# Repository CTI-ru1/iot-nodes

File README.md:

# iot-nodes

The overall design for the installation of IoT infrastructure has been built upon the open-source (hardware and software) Arduino
platform and consist of:
-  Environmental Devices (Digital and Analog versions)
-  Power Meter Devices
-  Gateway

The Eagles files and BOM of materials for the first for all the IoT nodes can be found it in the respective folders and the Arduino programs too. 
The Gateway program can be found it on (link)

Libraries
--
- App.h Has been designed to include the overall application on your Arduino IoT node program. Manage the add of the different sensor connected to the node, collect the data from each one and the update cloud values through the under tree network. You can find the code on this repository. 
- For each each sensor include it on the IoT node a specific class is include it. The specific classes using on this platform can be found on UberdustSensor folder. If you want to include new ones just create a new sensor class, include it in the UbersdustSensor.h file and programming the follow methods as you need. 
	-	periodic_check(): will be called on each Arduino loop. Include here, for example a code if you want to read a sensor value faster that each 20 sec and calculated the averaage value.
	-	check_and_send(void): will be called once each 20 seconds. Then all the collected values will be updated in the cloud. Here you must give to the status parameter the final value to be update on.
			
- At the network level: Treerouting.h library is using on the creation of a tree network between all the IoT nodes, with the Gateway as root. Can be downloaded from (link)
- At physical and data link later we use IEEE802.15.4 communication with XBee devices connected to each IoT node using the Arduino XBee(Link) library and XBeeRadio library(link). We must notice here that on both libraries need to be modified the serial port for using with the Arduino Por Micro.On this case you just need to change the code in order to read from Serial1.

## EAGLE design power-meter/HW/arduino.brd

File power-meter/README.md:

# power-meter
IoT nodes 3-phases Power Meter with electricity to monitor the consumption of a building. The power consumption meter measures the apparent power in a three
phase electrical installation and calculates its true power consumption re-motely.
Communication with the device is achieved using IEEE 802.15.4 trough a gateway.
Find the eagle files and BOM of materials necessary for reproducing the device on the HW folder and the specific Arduino program on SW folder.

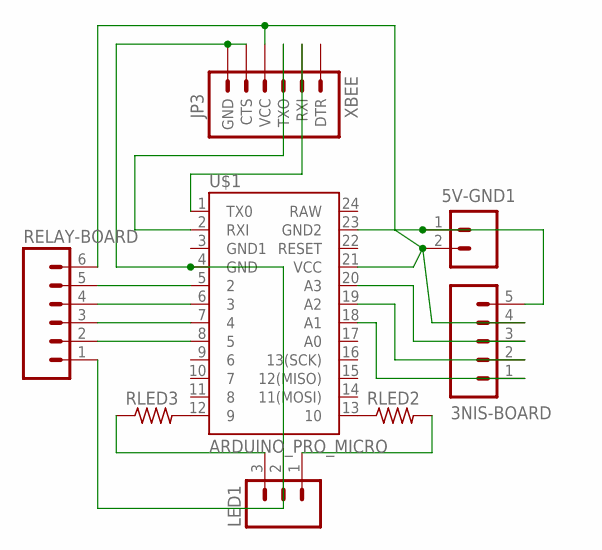
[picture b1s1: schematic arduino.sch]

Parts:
3NIS-BOARD: M05PTH; 1X05
5V-GND1: M025MM; SCREWTERMINAL-5MM-2
JP3: XBEE; 1X06
LED1: M03PTH; 1X03
RELAY-BOARD: M06SIP; 1X06
RLED2, RLED3: R-US_M0805; M0805
U$1: ARDUINO_PRO_MICRO

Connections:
unnamed: JP3.5 (CTS), JP3.6 (GND), LED1.2, RELAY-BOARD.1, U$1.4 (GND)
unnamed: 3NIS-BOARD.4, 5V-GND1.2, JP3.4 (VCC), RELAY-BOARD.6, U$1.21 (VCC)
unnamed: 3NIS-BOARD.3, U$1.20 (A3)
unnamed: RELAY-BOARD.5, U$1.5 (2)
unnamed: RELAY-BOARD.4, U$1.6 (3)
unnamed: RELAY-BOARD.3, U$1.7 (4)
unnamed: RELAY-BOARD.2, U$1.8 (5)
unnamed: JP3.2 (RXI), U$1.1 (TX0)
unnamed: 3NIS-BOARD.2, U$1.19 (A2)
unnamed: JP3.3 (TXO), U$1.2 (RXI)
unnamed: 3NIS-BOARD.1, U$1.18 (A1)
unnamed: RLED2.1, U$1.13 (10)
unnamed: RLED3.2, U$1.12 (9)
unnamed: LED1.1, RLED2.2
unnamed: LED1.3, RLED3.1
unnamed: 3NIS-BOARD.5, 5V-GND1.1, U$1.23 (GND2)

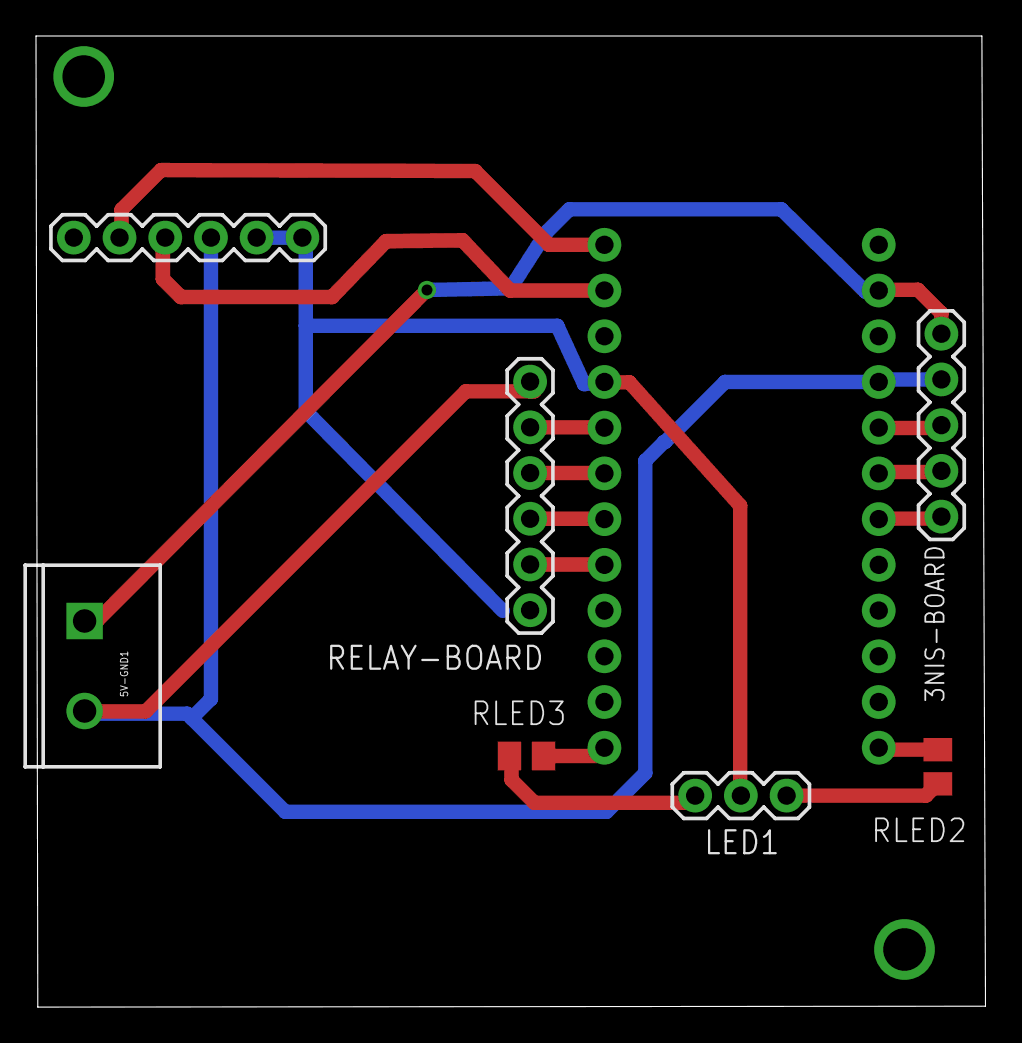
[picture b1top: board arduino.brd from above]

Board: 2 copper layers, 52.8 x 53.9 mm, 8 parts (0 on the bottom side), 16 nets.

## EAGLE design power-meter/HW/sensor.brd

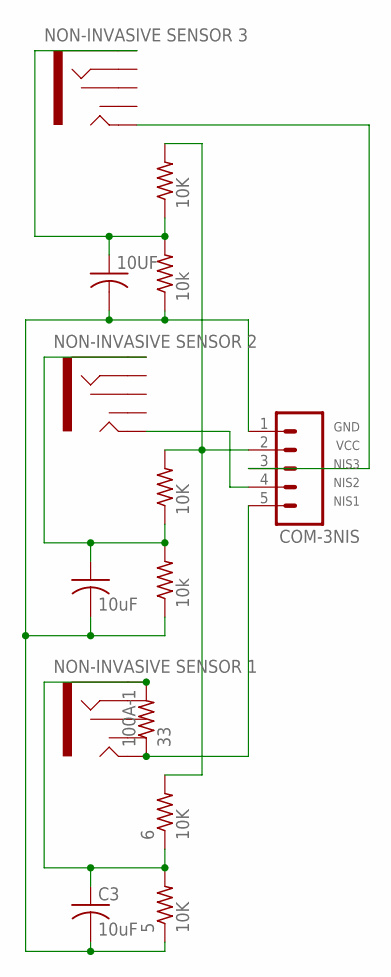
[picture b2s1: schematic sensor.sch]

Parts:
1, 3: 10k; M0805
2, 4, 5, 6: 10K; M0805
10UF: C-USC0805K; C0805K
100A-1: 33; M0805
C2, C3: 10uF; C0805K
COM-3NIS: M05PTH; 1X05
U1: NON-INVASIVE SENSOR 1; AUDIO-JACK
U2: NON-INVASIVE SENSOR 2; AUDIO-JACK
U3: NON-INVASIVE SENSOR 3; AUDIO-JACK

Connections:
unnamed: 2.2, 4.2, 6.2, COM-3NIS.2
unnamed 1: COM-3NIS.3, U3.TIP; also elsewhere on the board
unnamed 2: COM-3NIS.4, U2.TIP; also elsewhere on the board
unnamed: 100A-1.1, COM-3NIS.5, U1.TIP
unnamed 4: 1.2, 2.1, 10UF.1, U3.SLEEVE; also elsewhere on the board
unnamed 5: 3.2, 4.1, C2.1, U2.SLEEVE; also elsewhere on the board
unnamed: 5.2, 6.1, 100A-1.2, C3.1, U1.SLEEVE
unnamed: 1.1, 3.1, 5.1, 10UF.2, C2.2, C3.2, COM-3NIS.1

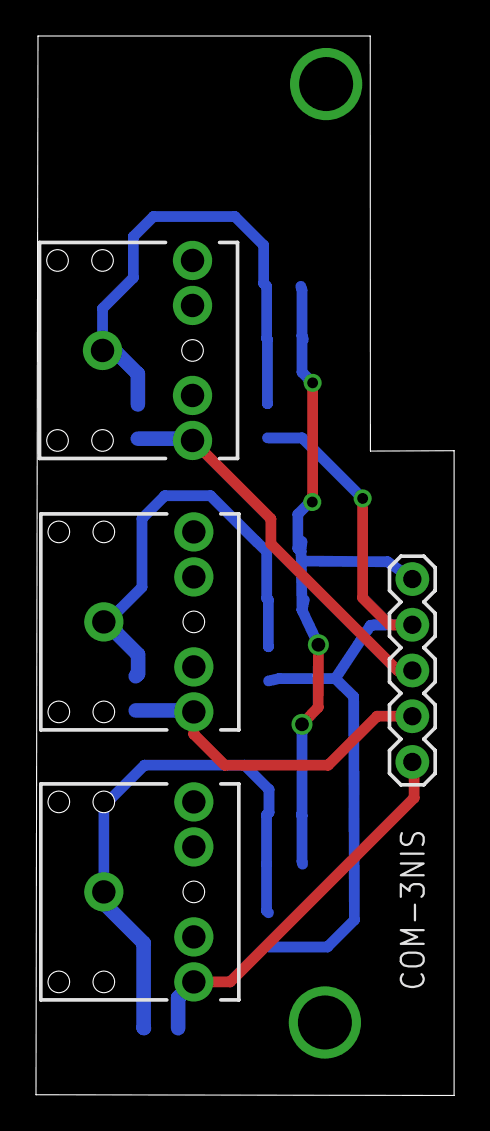
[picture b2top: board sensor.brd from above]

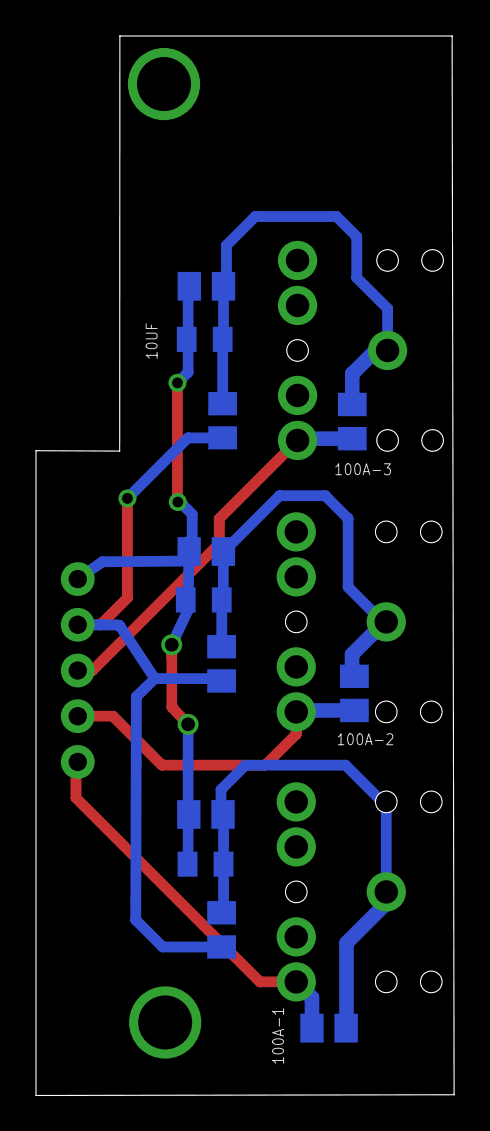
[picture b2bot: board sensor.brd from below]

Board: 2 copper layers, 23.2 x 58.9 mm, 16 parts (12 on the bottom side), 8 nets.

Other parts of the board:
100A-2, 100A-3: 33; M0805

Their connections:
unnamed 1: 100A-3.1; also elsewhere on the board
unnamed 2: 100A-2.1; also elsewhere on the board
unnamed 4: 100A-3.2; also elsewhere on the board
unnamed 5: 100A-2.2; also elsewhere on the board

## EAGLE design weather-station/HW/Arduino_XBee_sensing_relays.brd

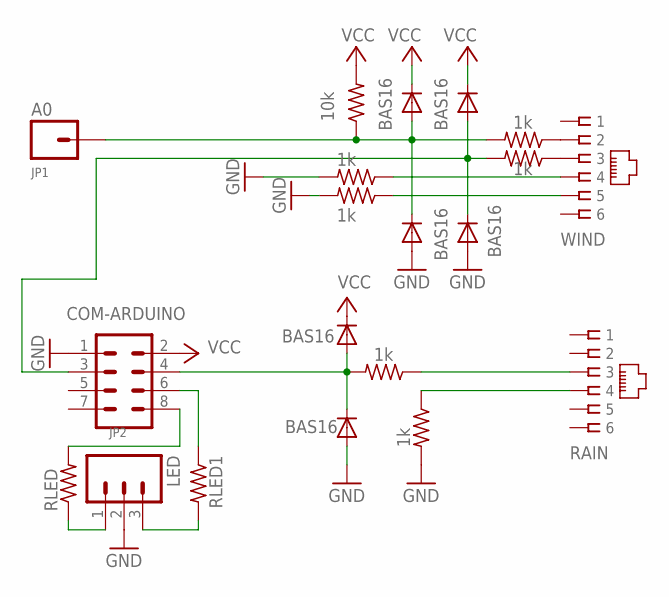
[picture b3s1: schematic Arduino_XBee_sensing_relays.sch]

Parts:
A0: JP1; 1X01
COM-ARDUINO: JP2; 2X4
D1, D2, D3, D4, D5, D6: BAS16; SOD-323
LED: M03PTH; 1X03
R1, R3, R4, R5, R7, R8: 1k; M0805
R2: 10k; M0805
RAIN: RAIN; RJ11-NO_SHIELD
RLED, RLED1: R-US_M0805; M0805
WIND: WIND; RJ11-NO_SHIELD

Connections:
GND: COM-ARDUINO.1, D2.2 (A), D4.2 (A), D6.2 (A), LED.2, R4.2, R5.2, R8.2
unnamed: COM-ARDUINO.4, D5.2 (A), D6.1 (C), R7.2
unnamed: LED.1, RLED.1
unnamed: R1.1, WIND.2
unnamed: R7.1, RAIN.3
unnamed: A0.1, D1.2 (A), D2.1 (C), R1.2, R2.1
unnamed: LED.3, RLED1.2
unnamed: COM-ARDUINO.6, RLED1.1
unnamed: COM-ARDUINO.8, RLED.2
unnamed: COM-ARDUINO.3, D3.2 (A), D4.1 (C), R3.2
unnamed: R4.1, WIND.4
unnamed: R5.1, WIND.5
unnamed: R8.1, RAIN.4
unnamed: R3.1, WIND.3
VCC: COM-ARDUINO.2, D1.1 (C), D3.1 (C), D5.1 (C), R2.2

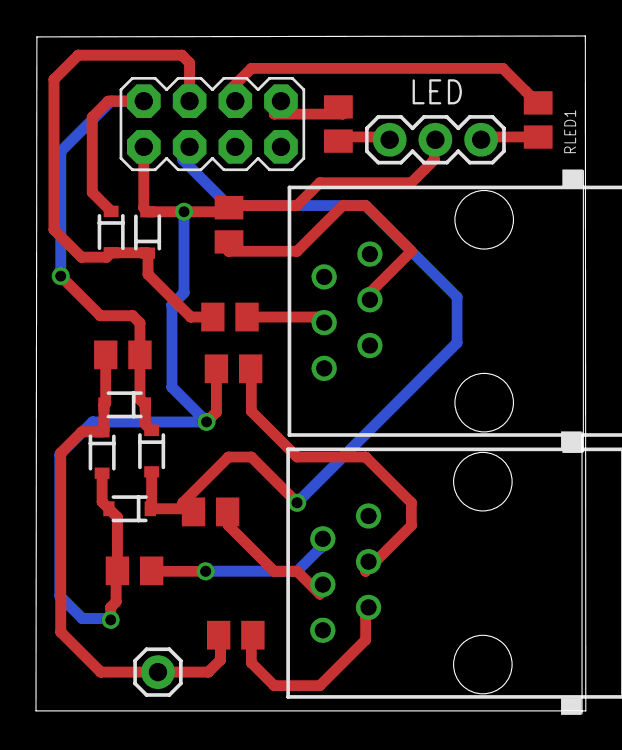
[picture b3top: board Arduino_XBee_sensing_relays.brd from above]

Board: 2 copper layers, 30.5 x 37.6 mm, 20 parts (0 on the bottom side), 15 nets.

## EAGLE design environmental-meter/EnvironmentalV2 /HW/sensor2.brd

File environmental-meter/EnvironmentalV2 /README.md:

# environmental-meter V1
IoT Environmental V2 include: 
- Grove-module with THO2 digital temperature and humidity sensor
- Grove-module with TSL2560 digital light sensor
- Grove-Sound sensor 
- PIR motion sensor.
Find the eagle files and BOM of materials necessary for reproducing the device on the HW folder and the specific Arduino program on SW folder. 
Is also necessary download the specific library for each digital module:
- Light module library: https://github.com/Seeed-Studio/Grove_Digital_Light_Sensor. 
- TH02 sensor has been modified and can be found it at https://github.com/CTI-ru1/Grove_Temper_Humidity_TH02. Here we have modified the original Seed-Studio library in order to 
can connect to the same I2C bus many digital sensors. We include methods to power on/off the module for guarantee just one module power each time on the I2C bus.

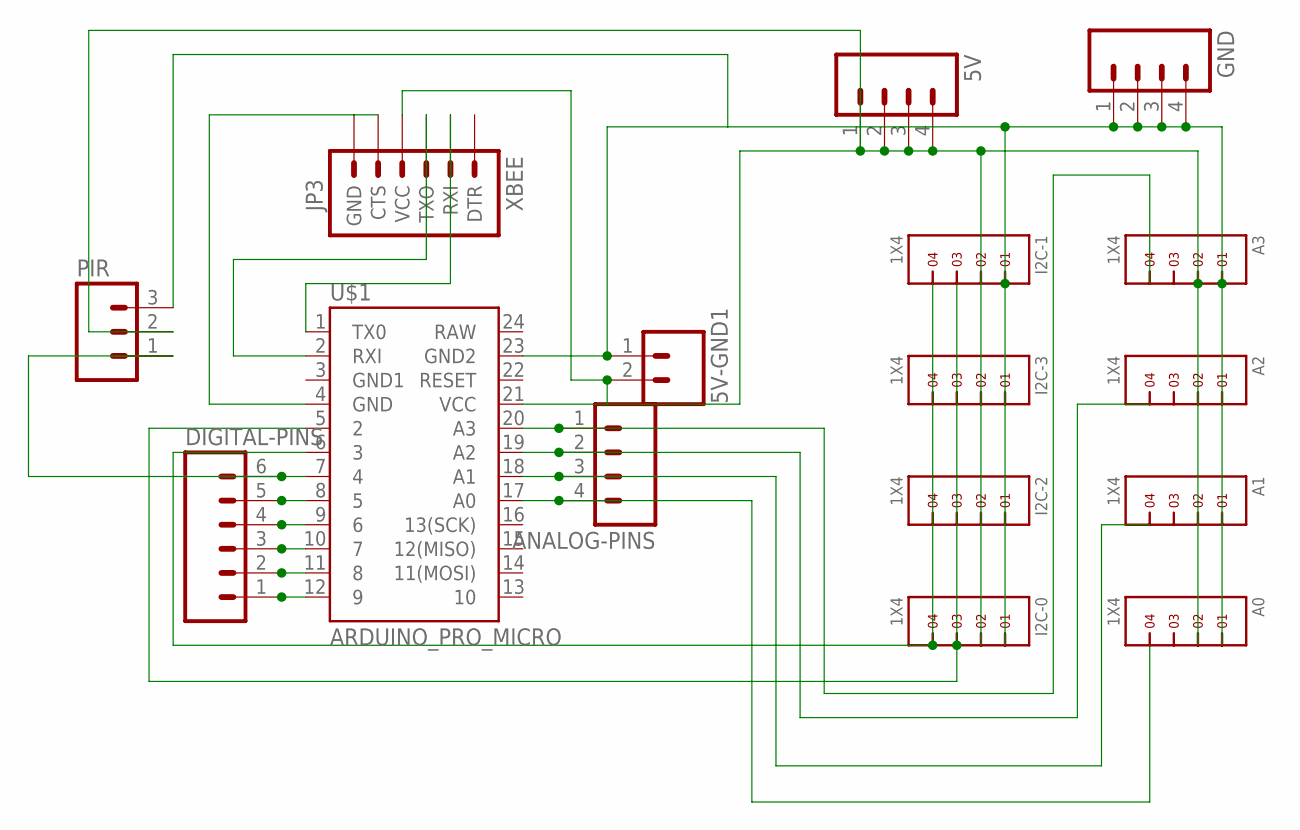
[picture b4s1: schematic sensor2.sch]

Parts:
5V: M04; 04P
5V-GND1: M025MM; SCREWTERMINAL-5MM-2
A0, A1, A2, A3: 1X4
ANALOG-PINS: M04; 04P
DIGITAL-PINS: M06; 06P
GND: M04; 04P
I2C-0, I2C-1, I2C-2, I2C-3: 1X4
JP3: XBEE; 1X06
PIR: M03; 03P
U$1: ARDUINO_PRO_MICRO

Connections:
GND: 5V-GND1.1, A0.1, A1.1, A2.1, A3.1, GND.1, GND.2, GND.3, GND.4, I2C-0.1, I2C-1.1, I2C-2.1, I2C-3.1, PIR.3, U$1.23 (GND2)
unnamed: I2C-0.4, I2C-1.4, I2C-2.4, I2C-3.4, U$1.6 (3)
unnamed: A3.4, ANALOG-PINS.1, U$1.20 (A3)
unnamed: JP3.5 (CTS), JP3.6 (GND), U$1.4 (GND)
unnamed: I2C-0.3, I2C-1.3, I2C-2.3, I2C-3.3, U$1.5 (2)
unnamed: 5V.1, 5V.2, 5V.3, 5V.4, 5V-GND1.2, A0.2, A1.2, A2.2, A3.2, I2C-0.2, I2C-1.2, I2C-2.2, I2C-3.2, JP3.4 (VCC), PIR.2, U$1.21 (VCC)
unnamed: A2.4, ANALOG-PINS.2, U$1.19 (A2)
unnamed: A1.4, ANALOG-PINS.3, U$1.18 (A1)
unnamed: JP3.2 (RXI), U$1.1 (TX0)
unnamed: A0.4, ANALOG-PINS.4, U$1.17 (A0)
unnamed: JP3.3 (TXO), U$1.2 (RXI)
unnamed: DIGITAL-PINS.2, U$1.11 (8)
unnamed: DIGITAL-PINS.3, U$1.10 (7)
unnamed: DIGITAL-PINS.4, U$1.9 (6)
unnamed: DIGITAL-PINS.5, U$1.8 (5)
unnamed: DIGITAL-PINS.6, PIR.1, U$1.7 (4)
unnamed: DIGITAL-PINS.1, U$1.12 (9)

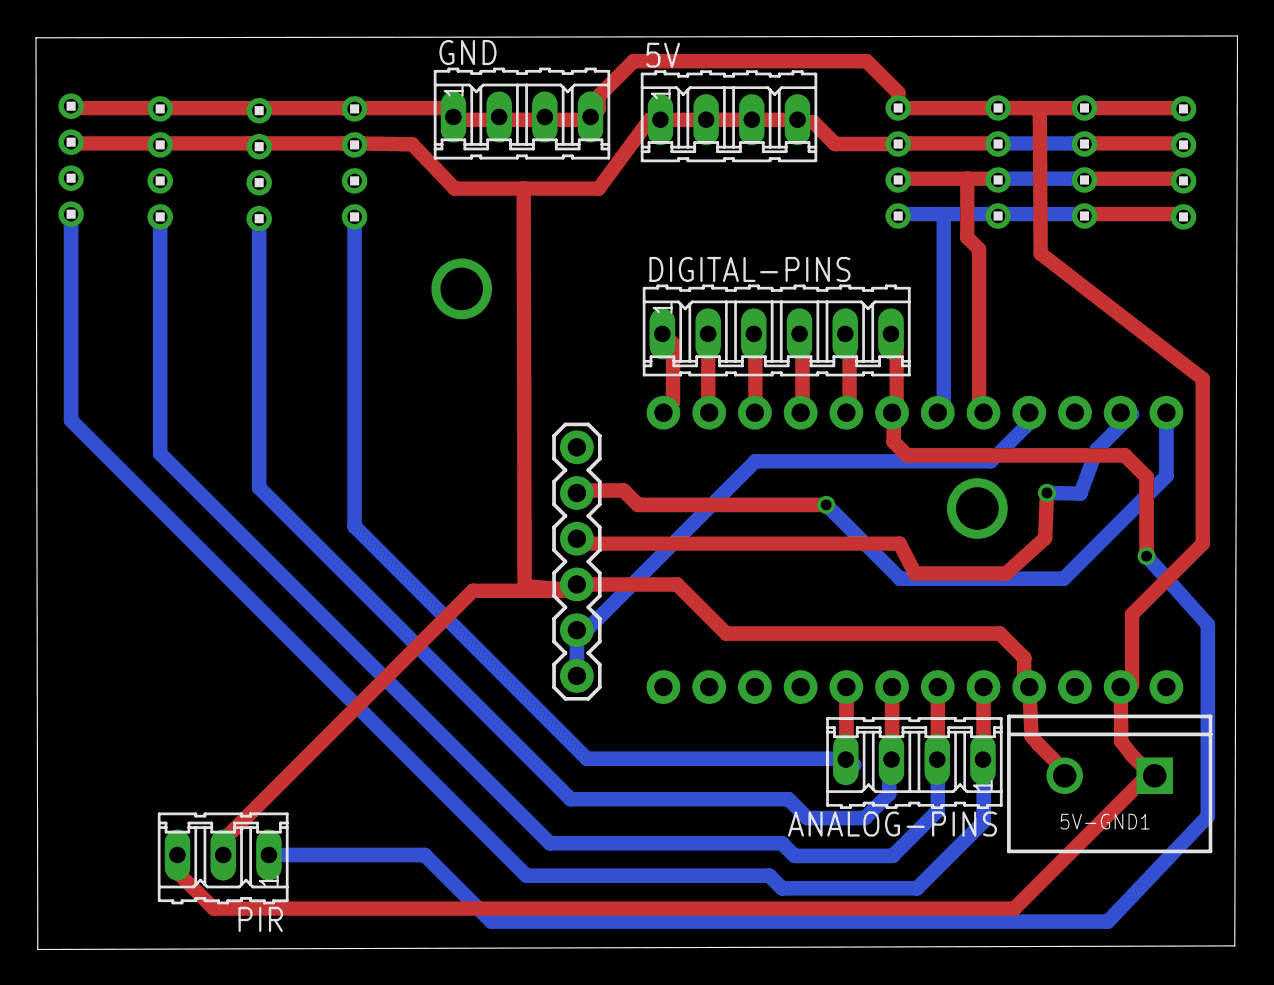
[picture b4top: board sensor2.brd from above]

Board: 2 copper layers, 66.8 x 50.7 mm, 16 parts (0 on the bottom side), 17 nets.

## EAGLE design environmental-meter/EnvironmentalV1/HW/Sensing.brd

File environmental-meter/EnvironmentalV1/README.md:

# environmental-meter V1
IoT Environmental V1 include: 

- LM35 analog temperature sensor
- HIH-4030 analog humidity sensor 
- photo-resistor
- Grove-Sound sensor 
- PIR motion sensor

Find the eagle files and BOM of materials necessary for reproducing the device on the HW folder and the specific Arduino program on SW folder.

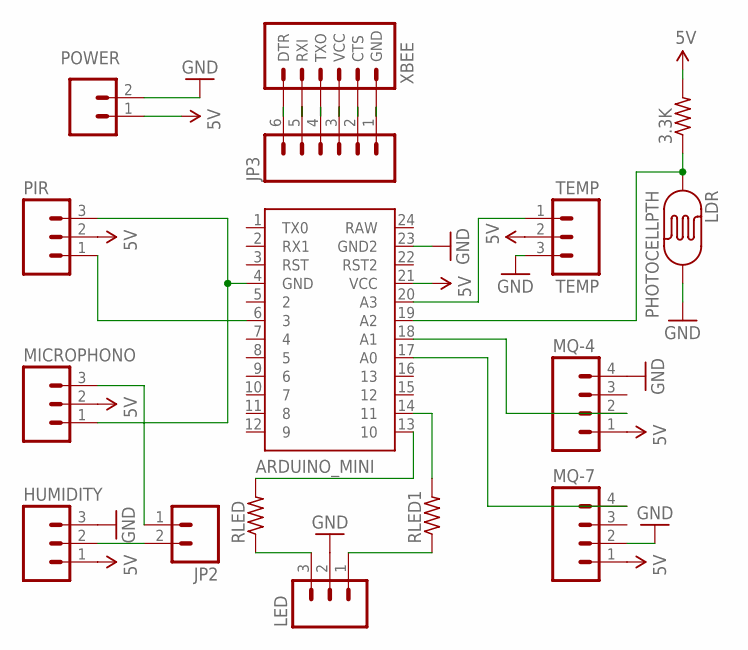
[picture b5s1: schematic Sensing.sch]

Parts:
3.3K: R-US_M0805; M0805
ARDUINO_MINI: ARDUINO_MINI
HUMIDITY: HUMIDITY; 1X03
JP2: M02PTH; 1X02
JP3: M06SIP; 1X06
LDR: PHOTOCELLPTH; PHOTOCELL
LED: M03PTH; 1X03
MICROPHONO: M03PTH; 1X03
MQ-4, MQ-7: M04PTH; 1X04
PIR: M03PTH; 1X03
POWER: M025MM; SCREWTERMINAL-5MM-2
RLED, RLED1: R-US_M0805; M0805
TEMP: TEMP; 1X03_NO_SILK
XBEE: ARDUINO_SERIAL_PROGRAMPTH; 1X06

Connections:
5V: 3.3K.2, ARDUINO_MINI.21 (VCC), HUMIDITY.1, MICROPHONO.2, MQ-4.1, MQ-7.1, PIR.2, POWER.1, TEMP.2
EXTRA_SENS_OUT: ARDUINO_MINI.20 (A3), TEMP.1
GND: ARDUINO_MINI.23 (GND2), HUMIDITY.3, LDR.2, LED.2, MQ-4.4, MQ-7.2, POWER.2, TEMP.3
HUMIDITY: HUMIDITY.2, JP2.2
MQ4_(CH4)_SENS_OUT: ARDUINO_MINI.18 (A1), MQ-4.2
MQ7_(CO)_SENS_OUT: ARDUINO_MINI.17 (A0), MQ-7.4
unnamed: LED.1, RLED1.1
unnamed: LED.3, RLED.1
unnamed: ARDUINO_MINI.6 (3), PIR.1
unnamed: ARDUINO_MINI.4 (GND), MICROPHONO.1, PIR.3
unnamed: JP3.6, XBEE.1 (DTR)
unnamed: JP3.5, XBEE.2 (RXI)
unnamed: JP3.4, XBEE.3 (TXO)
unnamed: JP3.3, XBEE.4 (VCC)
unnamed: JP3.2, XBEE.5 (CTS)
unnamed: JP3.1, XBEE.6 (GND)
unnamed: 3.3K.1, ARDUINO_MINI.19 (A2), LDR.1
unnamed: ARDUINO_MINI.14 (11), RLED1.2
unnamed: JP2.1, MICROPHONO.3
unnamed: ARDUINO_MINI.13 (10), RLED.2

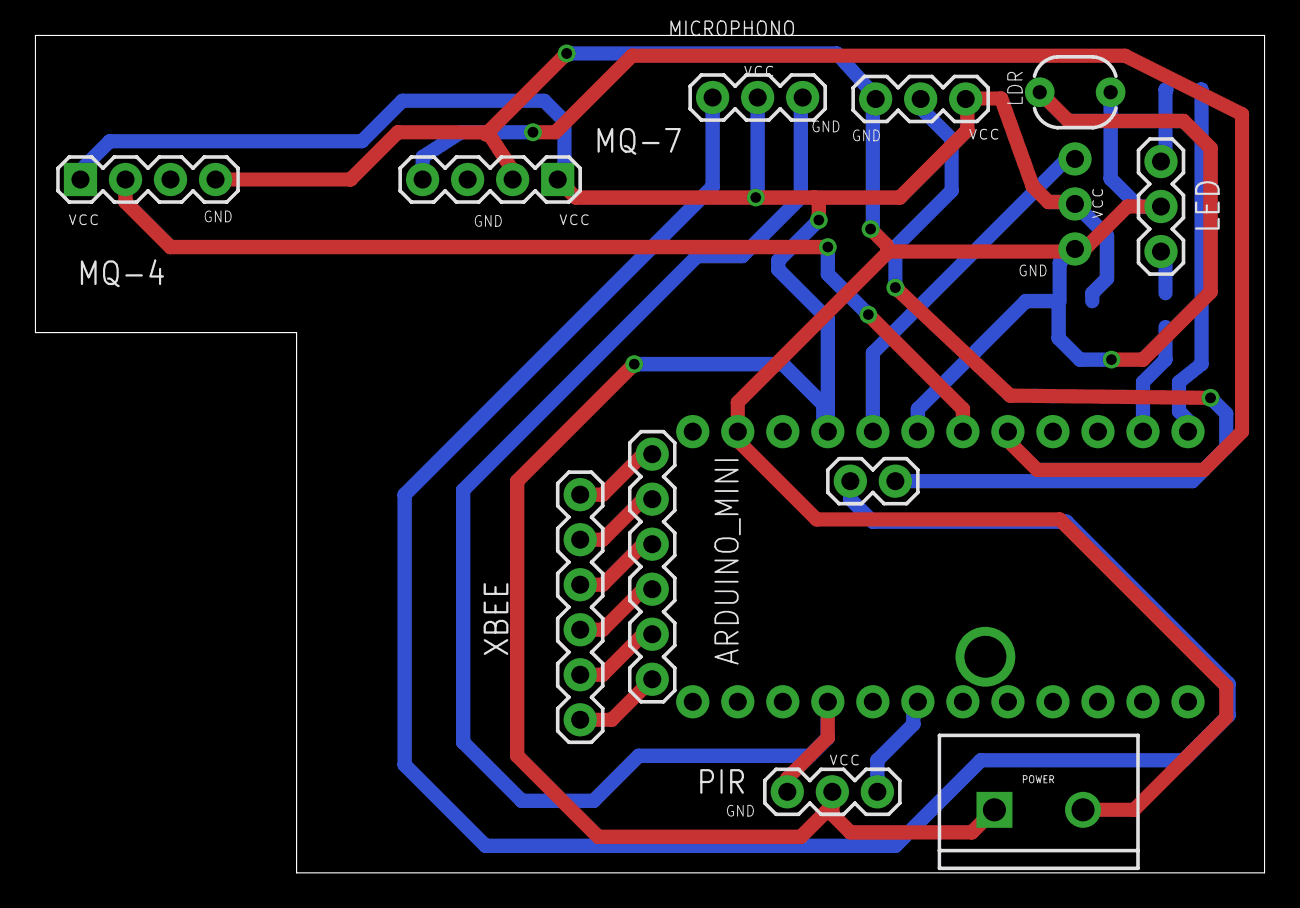
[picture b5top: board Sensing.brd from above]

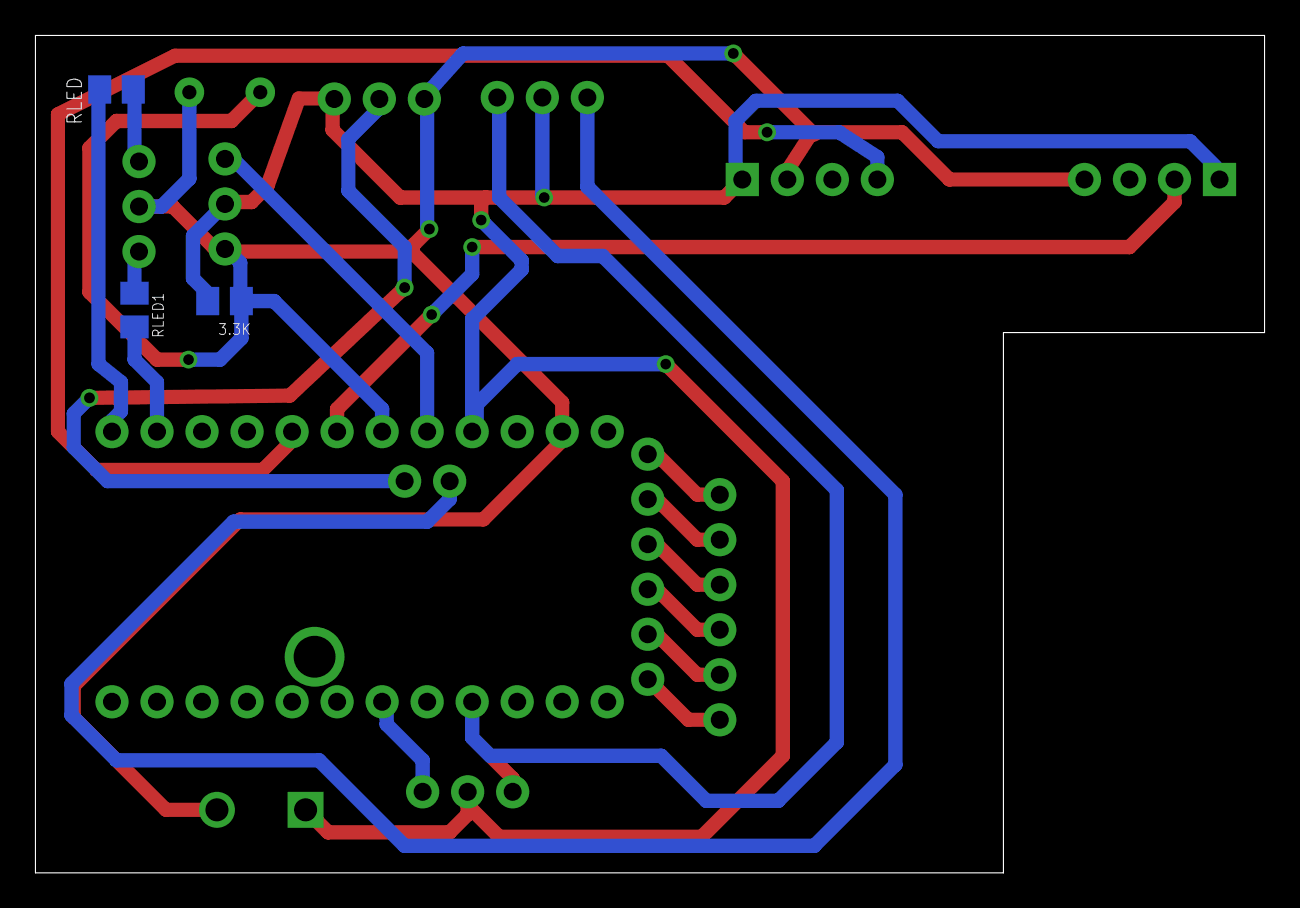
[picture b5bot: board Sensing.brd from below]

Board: 2 copper layers, 69.3 x 47.2 mm, 16 parts (3 on the bottom side), 20 nets.

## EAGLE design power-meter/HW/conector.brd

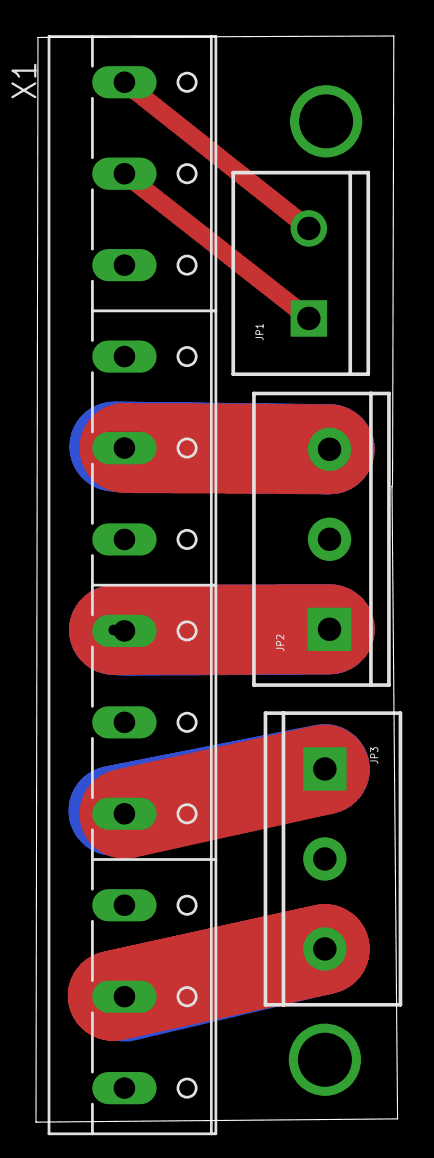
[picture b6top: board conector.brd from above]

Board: 2 copper layers, 20.1 x 60.3 mm, 4 parts (0 on the bottom side), 6 nets.

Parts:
JP1: M025MM; SCREWTERMINAL-5MM-2
JP2, JP3: SCREWTERMINAL-5MM-3
X1: W237-12P

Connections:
unnamed: JP1.2, X1.1
unnamed: JP2.3, X1.5
unnamed: JP1.1, X1.2
unnamed: JP3.1, X1.9
unnamed: JP3.3, X1.11
unnamed: JP2.1, X1.7

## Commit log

2016-11-21 directories
2016-11-22 Sw and HW files
2016-11-23 IoT node files
2016-11-23 readme
2016-11-28 IoT nodes
2016-11-28 IoT node
2018-01-10 EnvironmentalV2 update version
2018-01-10 Include Weather station HW
2018-01-17 Power meter PCBs without size lines
2018-05-09 CO2 Environmental Device

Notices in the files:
parts and their libraries:
SparkFun-Boards: Licensing: CC v3.0 Share-Alike You are welcome to use this library for commercial purposes.
